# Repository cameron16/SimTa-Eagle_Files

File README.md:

These files were used to print our PCB boards with the Bantam tools PCB milling machine. the laundry_on_off files correspond to the circuit that determines if a laundry machine is running or not. The product_compass file corresponds to the circuit that determines if a laundry machines door is open or not

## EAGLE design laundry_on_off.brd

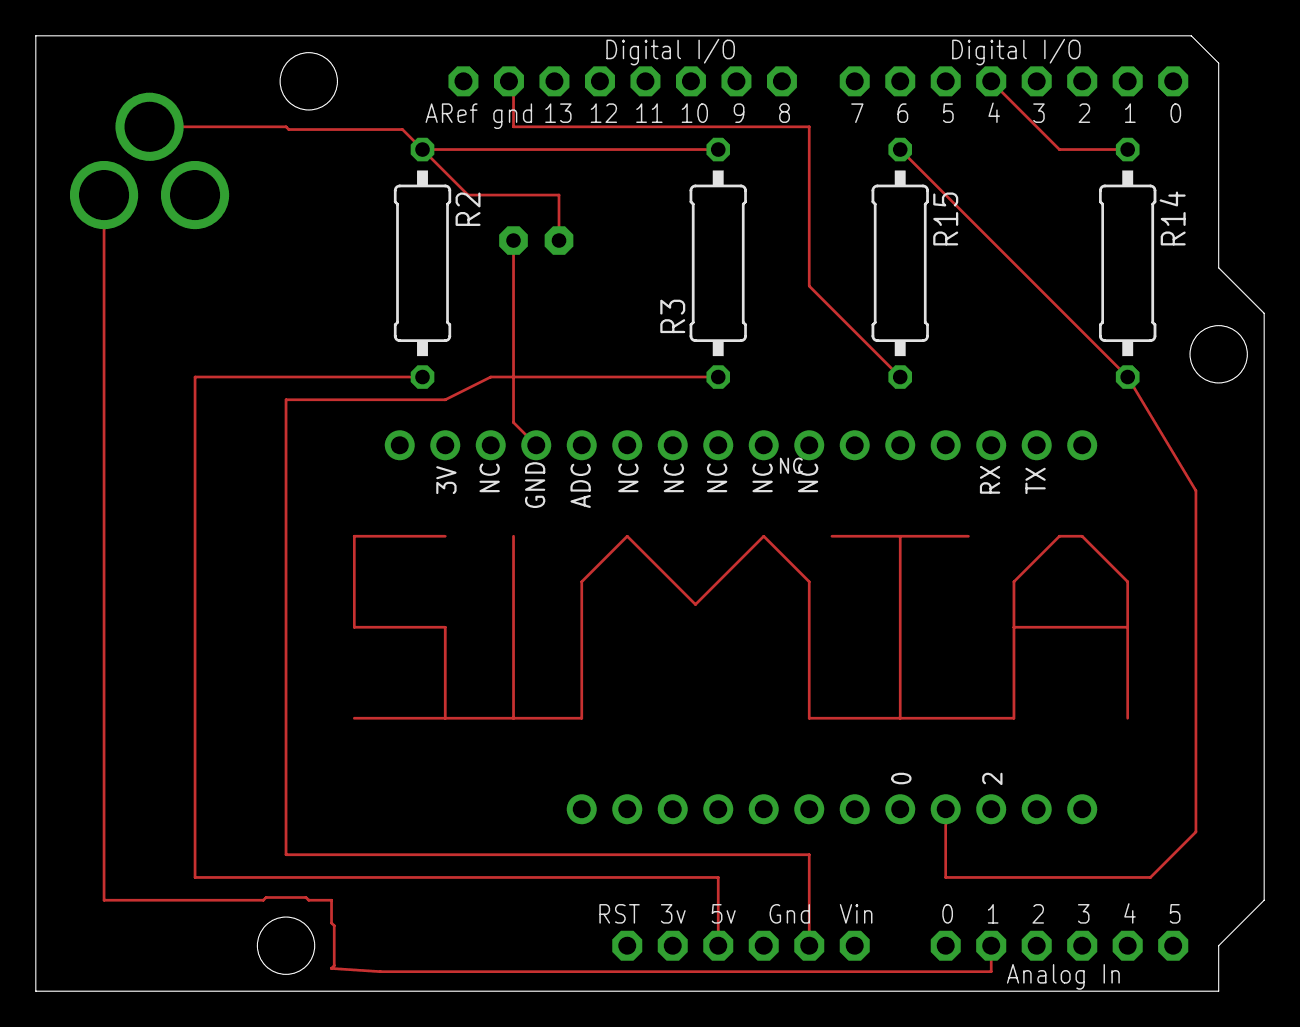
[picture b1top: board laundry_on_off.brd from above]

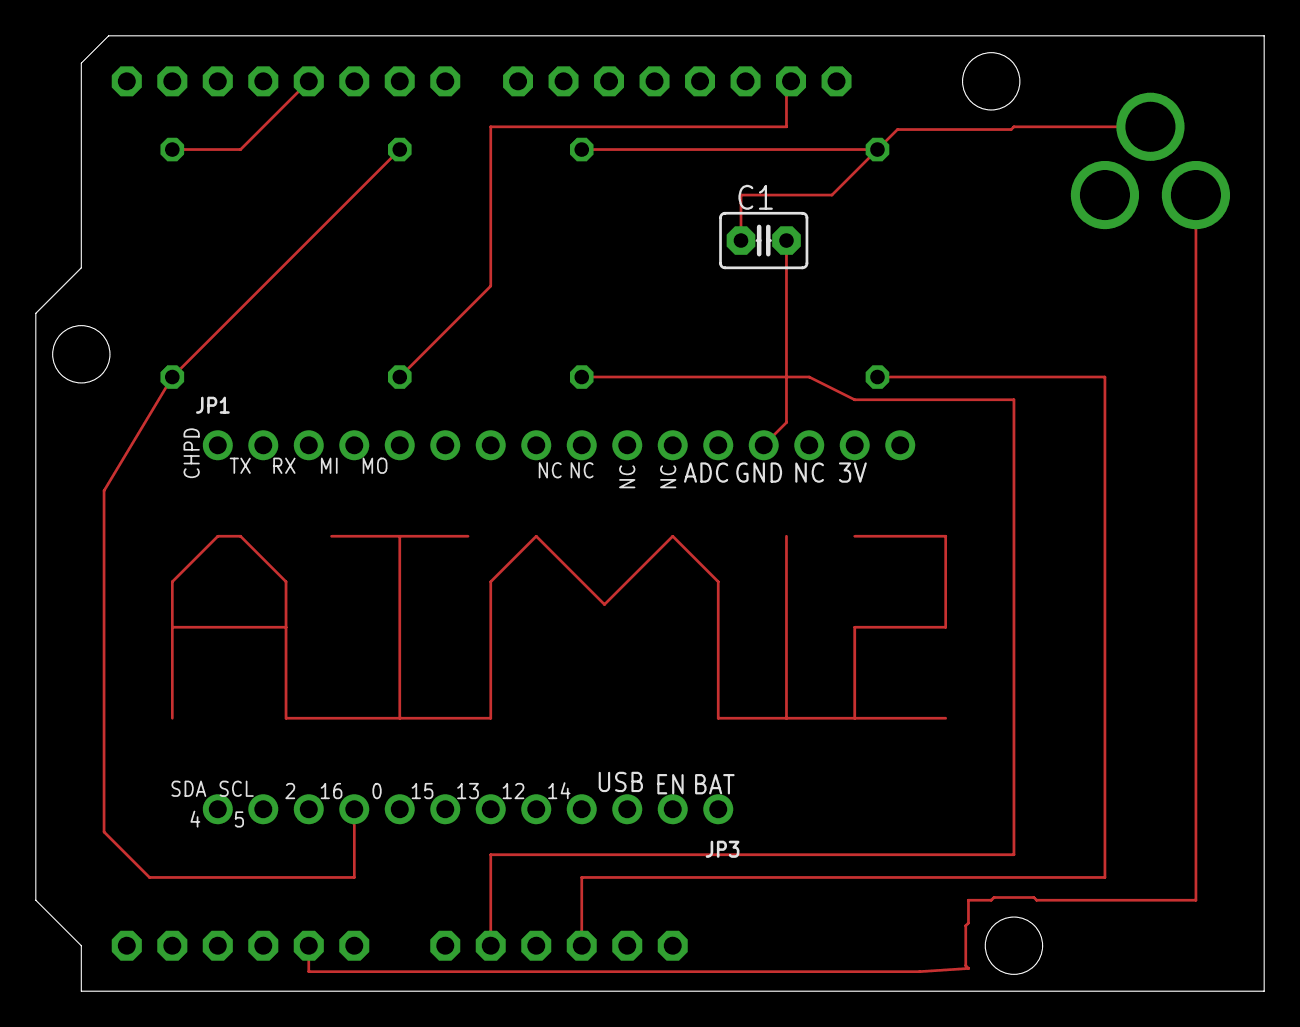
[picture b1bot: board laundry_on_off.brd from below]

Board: 2 copper layers, 68.6 x 53.3 mm, 8 parts (3 on the bottom side), 5 nets.

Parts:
C1: C2.5-3
JP1: 1X16_ROUND
JP3: 1X12_ROUND
R2, R3, R14, R15: 0309/12
U$1: ARDUINOUNO; ARDUINO

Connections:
GPIO16: JP3.9, R14.2, R15.1
unnamed: C1.1, R2.1, R3.2
unnamed: R2.2, U$1.5V
unnamed: R14.1, U$1.D4
S$1: C1.2, JP1.13, R3.1, U$1.GND1

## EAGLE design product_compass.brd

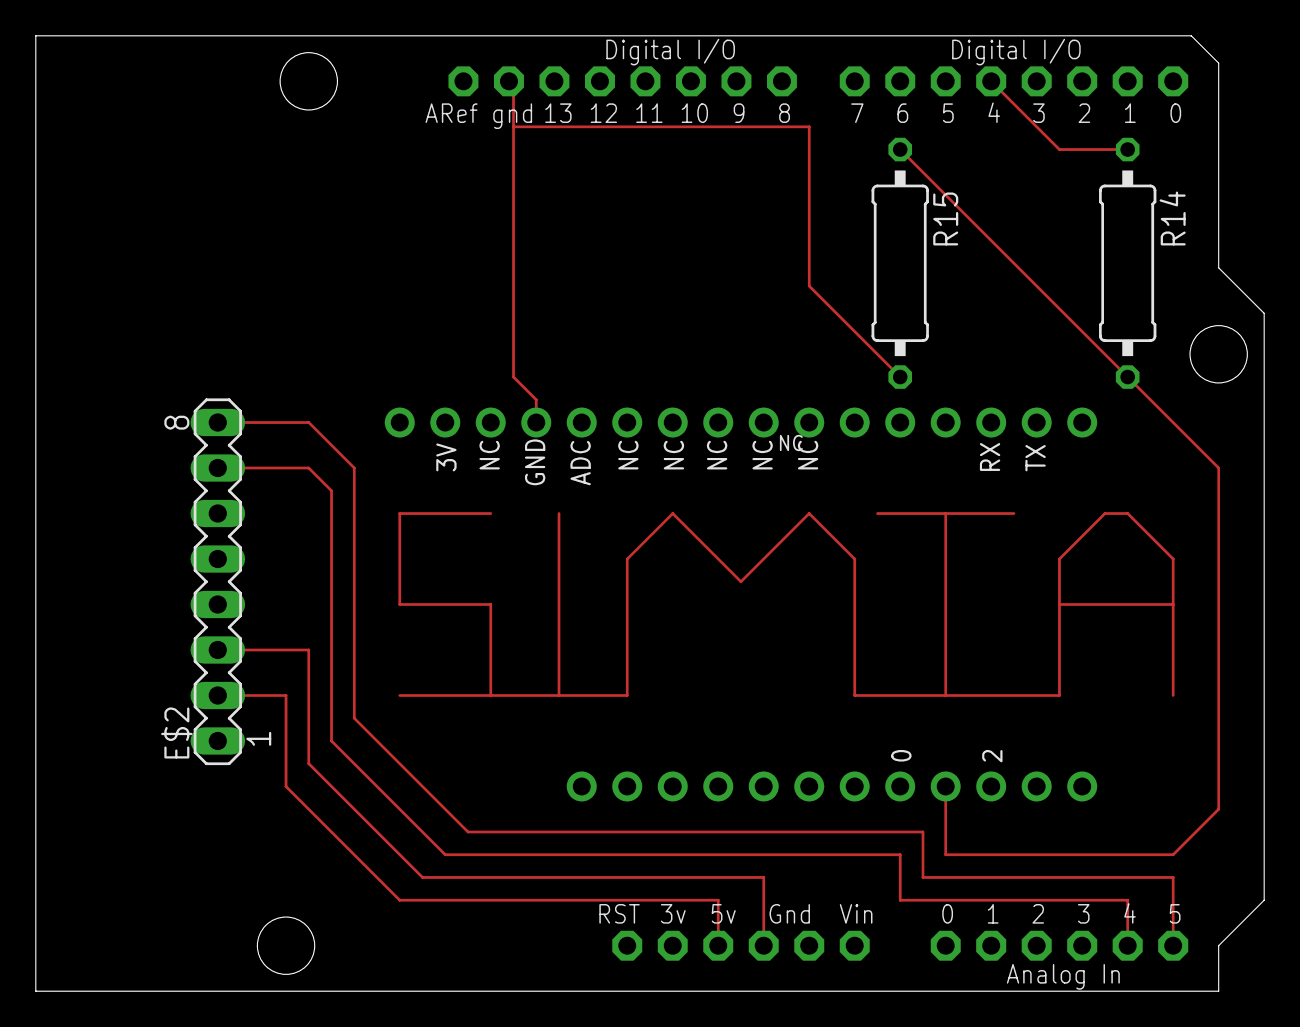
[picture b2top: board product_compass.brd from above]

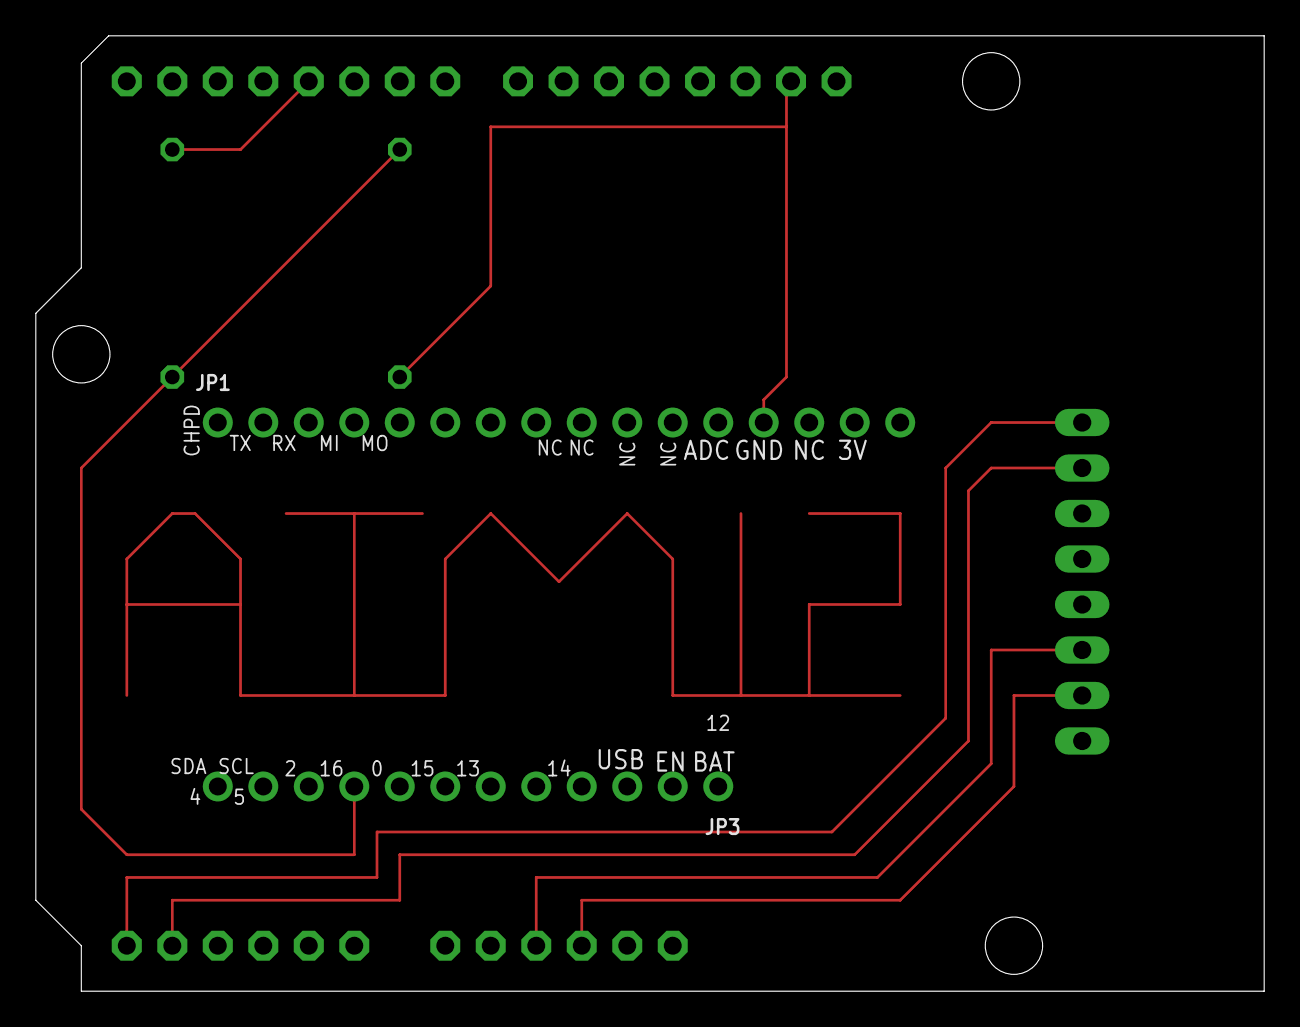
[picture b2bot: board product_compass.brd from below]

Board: 2 copper layers, 68.6 x 53.3 mm, 6 parts (2 on the bottom side), 7 nets.

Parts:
E$2: MA08-1
JP1: 1X16_ROUND
JP3: 1X12_ROUND
R14, R15: 0309/12
U$1: ARDUINOUNO; ARDUINO

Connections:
GND2: E$2.3, U$1.GND2
GPIO16: JP3.9, R14.2, R15.1
unnamed: R14.1, U$1.D4
S$1: E$2.7, U$1.A4
S$3: E$2.2, U$1.5V
S$4: JP1.13, R15.2
S$5: E$2.8, U$1.A5

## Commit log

2018-05-11 committing all work
2018-05-11 adding readme

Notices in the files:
parts and their libraries:
microbuilder: This work is placed in the public domain, and may be freely used for commercial and non-commercial work with the following conditions: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
